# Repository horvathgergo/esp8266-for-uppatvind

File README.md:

Newer version of the board based on an ESP32-C6 chip is available here: https://github.com/horvathgergo/esp32c6-for-uppatvind

# Smart Air Purifier (Project Uppåtvind)
Custom PCB based on ESP12-F (ESP8266) wifi module that serves as a smart controller for IKEA Uppåtvind Air Purifiers. It's embedded microcontroller enables you to incorporate your device to home automation systems (preferably to Home Assistant) or control it via custom mobile applications as it enjoys support from wide variety of firmwares. This project was implemented in two major phases. Hardware was designed with KiCAD, software is based on MicroPython.

About IKEA Uppåtvind: It is the newest air purifier of the swedish company, compact and even smaller than its older borther, Förnuftig. It effectively cleans the indoor air from harmful PM2.5 particles and pollen for cheap (price approx. EUR30). The device is optimised for small bedrooms and has three fan speed. 

Current status of the development: **Finalized**

Hardware: 
* [x] Schematic
* [x] Layout
* [x] BOM, CPL
* [x] 3D model 
* [x] Testing

Software:
* [X] MicroPython

## Hardware

PCB has the same size as the original one (70x36 mm) with mounting holes placed on it, thus it is supposed to fit just fine inside the plastic housing. Power supply of the fan is +24V, 0.8A. The board has a MC34063DR switching voltage regulator that provides the necessary power (+3v3, >500mA) for the wifi module. With the onboard physical button you can toggle the fan (turn on/off or even change speed). Two blue LEDs are connected to the ESP pins so it can indicate changes in operating mode. Note: to avoid unnecessary costs and save some space on the board physical filter reset button is not incorporated in this version as this function can be easily achieved through software side. 

The Purifier has a 4-pin PWM fan with +24VDC, 0.5A. The pins are POWER, GND, PWM, FG. PWM is a control pin for pulse width modulation and FG is the tacho pin for feedback purposes. The fan operates with a constant duty cycle of 50% and variable frequency between ca. 1-300Hz.

MCU programming: the board supports only UART programming via TX, RX pin headers (no USB interface), thus USB to TTL converter is necessary to upload firmware. It is recommended to supply the module via VIN and GND pins when programming. It is compatible with +5-24V supply (but +3V3 supply is not guaranteed to work as you may experience some voltage drop via the buck converter so make sure to provide enough voltage during flashing). Boot button is located on the right side of the wifi module.

BOM: Most of the chosen components are considered to be basic/standard parts at LCSC, however there are some extended components on the list (two large cap, inductor, esp, jst connectors and uart pin headers, tactile switch).

## Software

The software for Uppåtvind has been developed in Micropython. It enables the device to be controlled via mqtt while exploits Home Assistant mqtt autodiscovery features that provides with a smooth (almost zero config) setup process. 

More detailed description is available in this repo: https://github.com/horvathgergo/uPurifier

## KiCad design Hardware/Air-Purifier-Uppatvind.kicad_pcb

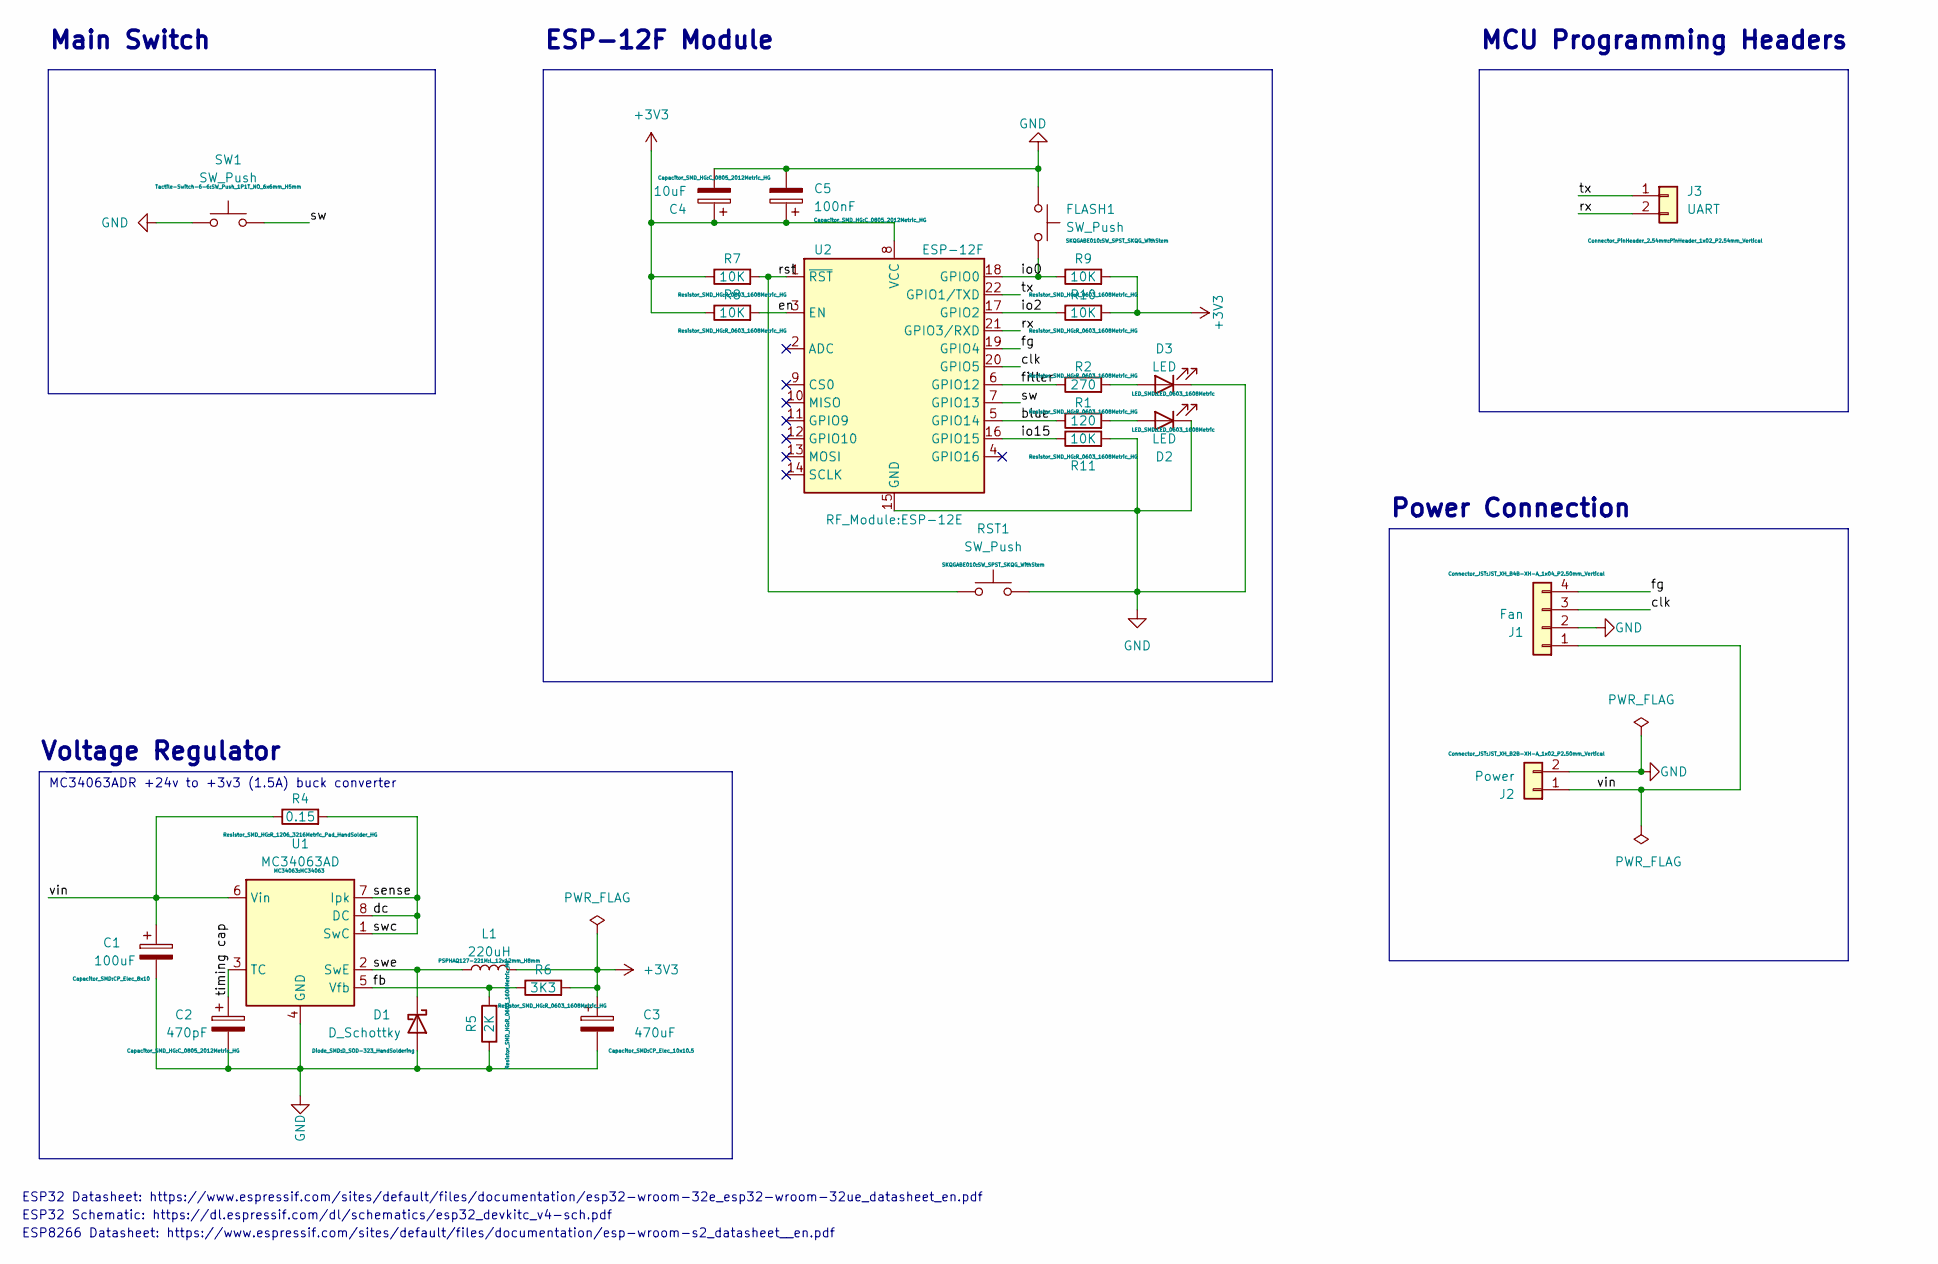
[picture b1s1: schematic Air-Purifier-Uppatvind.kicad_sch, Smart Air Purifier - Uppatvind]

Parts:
C1: 100uF; CP_Elec_8x10; LCSC C445063
C2: 470pF; C_0805_2012Metric_HG; LCSC C1743
C3: 470uF; CP_Elec_10x10.5; LCSC C72518
C4: 10uF; C_0805_2012Metric_HG; LCSC C15850
C5: 100nF; C_0805_2012Metric_HG; LCSC C28233
D1: D_Schottky; D_SOD-323_HandSoldering; LCSC C191023
D2, D3: LED; LED_0603_1608Metric; LCSC C72041
FLASH1: SW_Push; SW_SPST_SKQG_WithStem; LCSC C318884
J1: Fan; JST_XH_B4B-XH-A_1x04_P2.50mm_Vertical; LCSC C144395
J2: Power; JST_XH_B2B-XH-A_1x02_P2.50mm_Vertical; LCSC C161869
J3: UART; PinHeader_1x02_P2.54mm_Vertical
L1: 220uH; L_12x12mm_H8mm; LCSC C10151
R1: 120; R_0603_1608Metric_HG; LCSC C22787
R2: 270; R_0603_1608Metric_HG; LCSC C22966
R4: 0.15; R_1206_3216Metric_Pad_HandSolder_HG; LCSC C247454
R5: 2K; R_0603_1608Metric_HG; LCSC C22975
R6: 3K3; R_0603_1608Metric_HG; LCSC C22978
R7, R8, R9, R10, R11: 10K; R_0603_1608Metric_HG; LCSC C25804
RST1: SW_Push; SW_SPST_SKQG_WithStem; LCSC C318884
SW1: SW_Push; SW_Push_1P1T_NO_6x6mm_H5mm; LCSC C255812
U1: MC34063AD; MC34063; LCSC C32078
U2: ESP-12F; ESP-12E; LCSC C82891

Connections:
+3V3: C3.1, C4.1, C5.1, L1.2, R6.2, R7.1, R8.1, R9.2, R10.2, U2.8 (VCC)
/blue: R1.1, U2.5 (GPIO14)
/clk: J1.3, U2.20 (GPIO5)
/dc: R4.2, U1.1 (SwC), U1.7 (Ipk), U1.8 (DC)
/en: R8.2, U2.3 (EN)
/fb: R5.2, R6.1, U1.5 (Vfb)
/fg: J1.4, U2.19 (GPIO4)
/filter: R2.1, U2.6 (GPIO12)
/io0: FLASH1.2, R9.1, U2.18 (GPIO0)
/io2: R10.1, U2.17 (GPIO2)
/io15: R11.1, U2.16 (GPIO15)
/rst: R7.2, RST1.1, U2.1 (~RST)
/rx: J3.2, U2.21 (GPIO3/RXD)
/sw: SW1.2, U2.7 (GPIO13)
/swe: D1.1 (K), L1.1, U1.2 (SwE)
/timing cap: C2.1, U1.3 (TC)
/tx: J3.1, U2.22 (GPIO1/TXD)
/vin: C1.1, J1.1, J2.1, R4.1, U1.6 (Vin)
GND: C1.2, C2.2, C3.2, C4.2, C5.2, D1.2 (A), D2.1 (K), D3.1 (K), FLASH1.1, J1.2, J2.2, R5.1, R11.2, RST1.2, SW1.1, U1.4 (GND), U2.15 (GND)
unnamed: D2.2 (A), R1.2
unnamed: D3.2 (A), R2.2

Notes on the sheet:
MC34063ADR +24v to +3v3 (1.5A) buck converter
ESP32 Schematic: https://dl.espressif.com/dl/schematics/esp32_devkitc_v4-sch.pdf
ESP-12F Module
Voltage Regulator
Power Connection
MCU Programming Headers
ESP8266 Datasheet: https://www.espressif.com/sites/default/files/documentation/esp-wroom-s2_datasheet__en.pdf
ESP32 Datasheet: https://www.espressif.com/sites/default/files/documentation/esp32-wroom-32e_esp32-wroom-32ue_datasheet_en.pdf
Main Switch

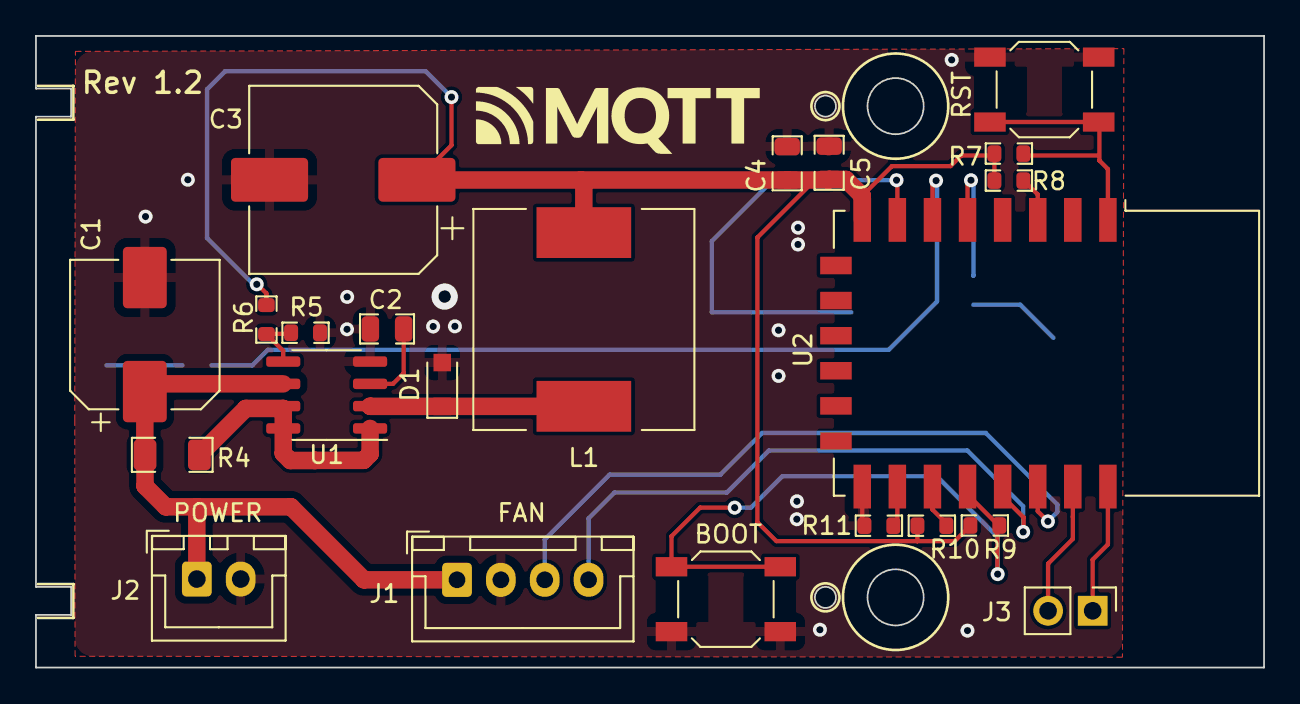
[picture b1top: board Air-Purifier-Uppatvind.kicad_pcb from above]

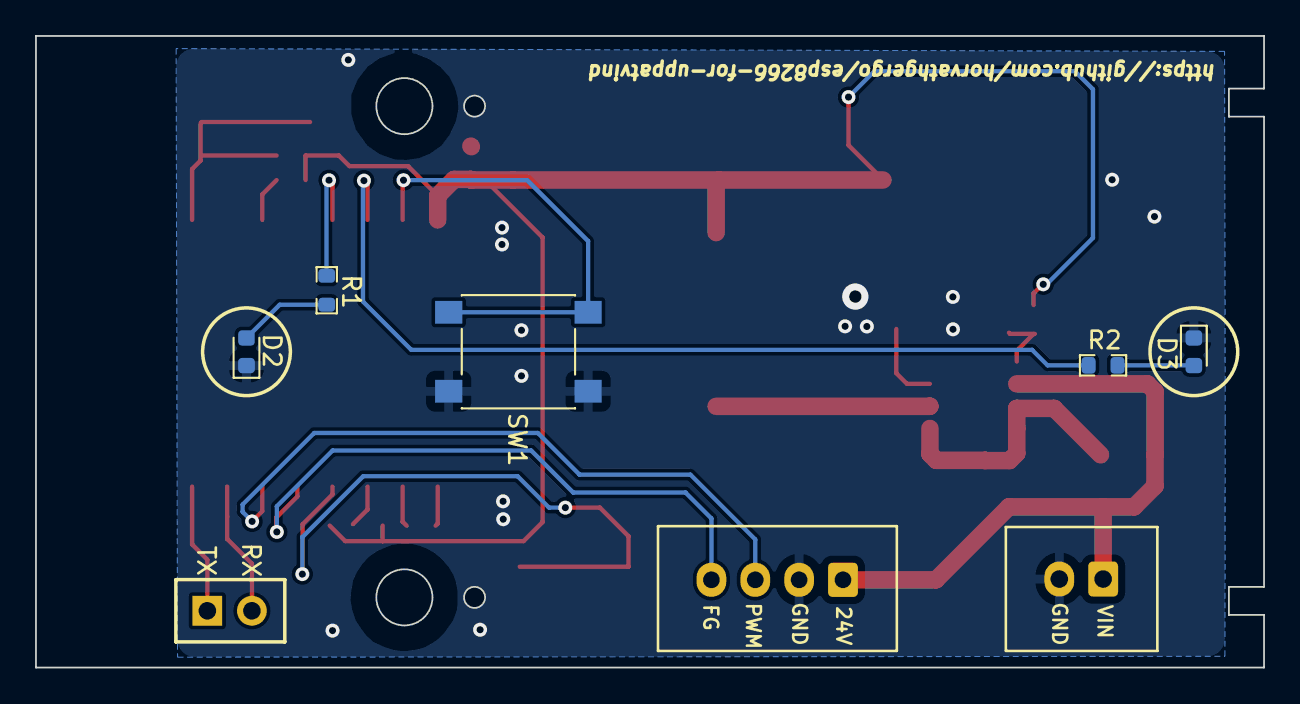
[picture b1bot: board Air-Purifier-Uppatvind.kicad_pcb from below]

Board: 2 copper layers, 70.0 x 36.0 mm, 27 parts (5 on the bottom side), 21 nets.

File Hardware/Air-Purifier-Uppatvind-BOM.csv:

Comment,Designator,Footprint,LCSC Part Number
100uF,C1,Capacitor_SMD:CP_Elec_8x10,C445063
470pF,C2,Capacitor_SMD_HG:C_0805_2012Metric_HG,C1743
470uF,C3,Capacitor_SMD:CP_Elec_10x10.5,C72518
10uF,C4,Capacitor_SMD_HG:C_0805_2012Metric_HG,C15850
100nF,C5,Capacitor_SMD_HG:C_0805_2012Metric_HG,C28233
D_Schottky,D1,Diode_SMD:D_SOD-323_HandSoldering,C191023
LED,"D2, D3",LED_SMD:LED_0603_1608Metric,C72041
SW_Push,"FLASH1, RST1",SKQGABE010:SW_SPST_SKQG_WithStem,C318884
Fan,J1,Connector_JST:JST_XH_B4B-XH-A_1x04_P2.50mm_Vertical,C144395
Power,J2,Connector_JST:JST_XH_B2B-XH-A_1x02_P2.50mm_Vertical,C161869
UART,J3,Connector_PinHeader_2.54mm:PinHeader_1x02_P2.54mm_Vertical,
220uH,L1,PSPHAQ127-221M:L_12x12mm_H8mm,C10151
120,R1,Resistor_SMD_HG:R_0603_1608Metric_HG,C22787
270,R2,Resistor_SMD_HG:R_0603_1608Metric_HG,C22966
0.15,R4,Resistor_SMD_HG:R_1206_3216Metric_Pad_HandSolder_HG,C247454
2K,R5,Resistor_SMD_HG:R_0603_1608Metric_HG,C22975
3K3,R6,Resistor_SMD_HG:R_0603_1608Metric_HG,C22978
10K,"R7, R8, R9, R10, R11",Resistor_SMD_HG:R_0603_1608Metric_HG,C25804
SW_Push,SW1,Tactile-Switch-6-6:SW_Push_1P1T_NO_6x6mm_H5mm,C255812
MC34063AD,U1,MC34063:MC34063,C32078
ESP-12F,U2,RF_Module:ESP-12E,C82891

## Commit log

2022-12-31 Update README.md
    Initialize PCBHome logo
2023-01-28 Create Hardware
2023-01-28 Added BOM file
2023-01-28 Added CPL files
2023-01-28 Added Schematic v1.0
2023-01-28 Added Layout v1.0
2023-01-28 Added Gerber
2023-01-28 Added CPL file
2023-01-28 BOM update
2023-01-29 Add v1.1 files
2023-02-06 Update README.md
    Minor fix
2023-04-12 added rev1.2 3D models
2023-04-12 Added files (board v1.2)
2023-04-15 Added Schematics and Layout (board v1.2)
